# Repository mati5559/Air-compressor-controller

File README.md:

# Air-compressor-controller

Controller for my DIY air compressor

# Description

I made air compressor from two washing machine's motors, some tank, air pump and a few other elements. 
Those motors are universal brush motors, so i need some controller to stabilize their speed. 
This controller stabilises motors speed with PID algorithm, turns them on and off at specified pressure and have some other features:
- temperature protection
- oil change interval reminder (It measures working time and turn on LED when oil should be changed) 
- fan control 
- soft start (PID)
- overload protection

In software directory is Eclipse C++ project.
In hardware directory are board and schematic. It should be run with AutoDesk Eagle. 

# WARNING

DIY air compressors are very dangerous. 
There is high voltage in this circuit that can kill you.
High pressure tank also can be dangerous. It can explode.

I did it at my own risk for science and fun. Do not do this by yourself!

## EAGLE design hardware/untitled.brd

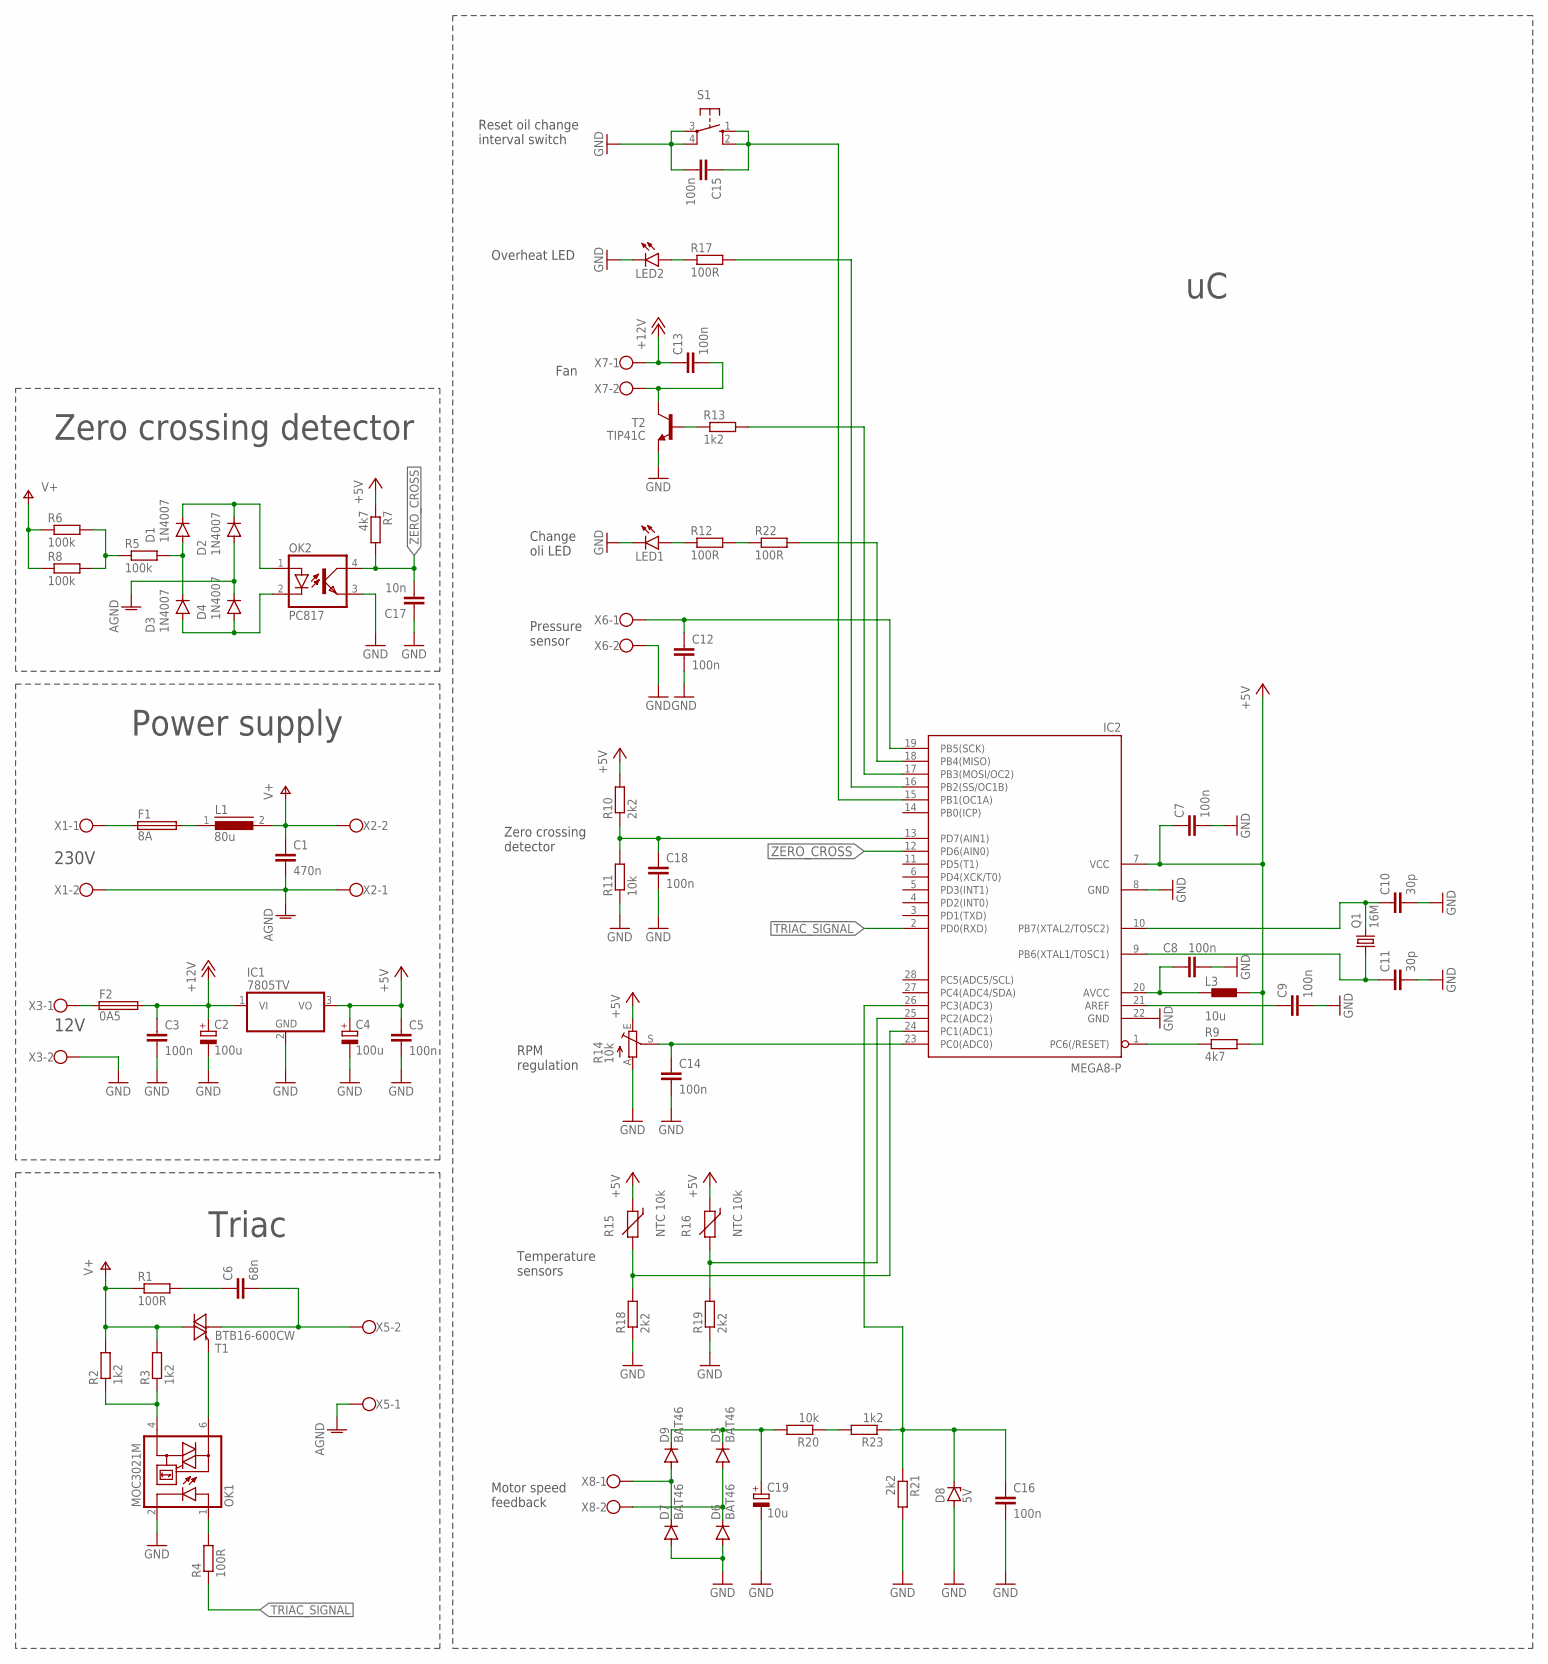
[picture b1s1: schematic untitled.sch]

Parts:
C1: 470n; C22.5B7
C2, C4: 100u; E3,5-8
C3, C5, C7, C8, C9, C12, C13, C14, C15, C16, C18: 100n; C5B3
C6: 68n; C150-084X183
C10, C11: 30p; C5B3
C17: 10n; C5B3
C19: 10u; E2,5-6
D1, D2, D3, D4: 1N4007; DO41-10
D5, D6, D7, D9: BAT46; DO34-7
D8: 5V; DO34Z7
F1: 8A; SHK20L
F2: 0A5; SHK20L
IC1: 7805TV; TO220V
IC2: MEGA8-P; DIL28-3
L1: 80u; SFT1030
L3: 10u; BL01RN1A
LED1, LED2: LED5MM
OK1: MOC3021M; DIL06
OK2: PC817; DIL04
Q1: 16M; HC49/S
R1, R4, R12, R17, R22: 100R; 0204/7
R2, R3, R13, R23: 1k2; 0204/7
R5, R6, R8: 100k; 0204/7
R7, R9: 4k7; 0204/7
R10, R18, R19, R21: 2k2; 0204/7
R11, R20: 10k; 0204/7
R14: 10k; RJ9W
R15, R16: NTC 10k; R-7,5
S1: 10-XX; B3F-10XX
T1: BTB16-600CW; TO220BV
T2: TIP41C; TO220V
X1, X2, X3, X5, X6, X7, X8: W237-102

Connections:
+5V: C4.+, C5.1, C7.1, IC1.3 (VO), IC2.7 (VCC), L3.2, R7.1, R9.2, R10.2, R14.E, R15.1, R16.1
+12V: C2.+, C3.1, C13.1, F2.2A, IC1.1 (VI), X7.1
AGND: C1.2, D2.A, D4.C, X1.2, X2.1, X5.1
GND: C2.-, C3.2, C4.-, C5.2, C7.2, C8.2, C9.2, C10.2, C11.2, C12.2, C14.2, C15.2, C16.2, C17.1, C18.2, C19.-, D6.A, D7.A, D8.A, IC1.2 (GND), IC2.8 (GND), IC2.22 (GND), LED1.K (C), LED2.K (C), OK1.2 (C), OK2.3 (EMIT), R11.1, R14.A, R18.1, R19.1, R21.2, S1.3, S1.4 (P1), T2.3 (E), X3.2, X6.2
unnamed: F1.1A, X1.1
unnamed: F1.2A, L1.1
unnamed: OK1.6 (A2), T1.G
unnamed: C6.2, T1.T1 (A1), X5.2
unnamed: C6.1, R1.2
unnamed: OK1.4 (A1), R2.1, R3.1
unnamed: F2.1A, X3.1
unnamed: OK1.1 (A), R4.2
unnamed: D1.C, D2.C, OK2.1 (A)
unnamed: D3.A, D4.A, OK2.2 (C)
unnamed: R5.1, R6.2, R8.2
unnamed: D7.C, D9.A, X8.1
unnamed: C18.1, IC2.13 (PD7(AIN1)), R10.1, R11.2
unnamed: C8.1, IC2.20 (AVCC), L3.1
unnamed: C9.1, IC2.21 (AREF)
unnamed: IC2.1 (PC6(/RESET)), R9.1
unnamed: C10.1, IC2.10 (PB7(XTAL2/TOSC2)), Q1.2
unnamed: C11.1, IC2.9 (PB6(XTAL1/TOSC1)), Q1.1
unnamed: C12.1, IC2.19 (PB5(SCK)), X6.1
unnamed: LED1.A, R12.1
unnamed: IC2.18 (PB4(MISO)), R22.2
unnamed: C13.2, T2.2 (C), X7.2
unnamed: R13.1, T2.1 (B)
unnamed: IC2.17 (PB3(MOSI/OC2)), R13.2
unnamed: C14.1, IC2.23 (PC0(ADC0)), R14.S
unnamed: IC2.24 (PC1(ADC1)), R15.2, R18.2
unnamed: IC2.25 (PC2(ADC2)), R16.2, R19.2
unnamed: LED2.A, R17.1
unnamed: IC2.16 (PB2(SS/OC1B)), R17.2
unnamed: C19.+, D5.C, D9.C, R20.2
unnamed: C15.1, IC2.15 (PB1(OC1A)), S1.1 (S), S1.2 (S1)
unnamed: D1.A, D3.C, R5.2
unnamed: D5.A, D6.C, X8.2
unnamed: C16.1, D8.C, IC2.26 (PC3(ADC3)), R21.1, R23.1
unnamed: R12.2, R22.1
unnamed: R20.1, R23.2
TRIAC_SIGNAL: IC2.2 (PD0(RXD)), R4.1
V+: C1.1, L1.2, R1.1, R2.2, R3.2, R6.1, R8.1, T1.T2 (A2), X2.2
ZERO_CROSS: C17.2, IC2.12 (PD6(AIN0)), OK2.4 (COL), R7.2

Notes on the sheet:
230V
12V
Power supply
Triac
Zero crossing detector
Pressure sensor
Change oli LED
Fan
RPM regulation
Temperature sensors
Overheat LED
Reset oil change interval switch
Motor speed feedback
Zero crossing detector

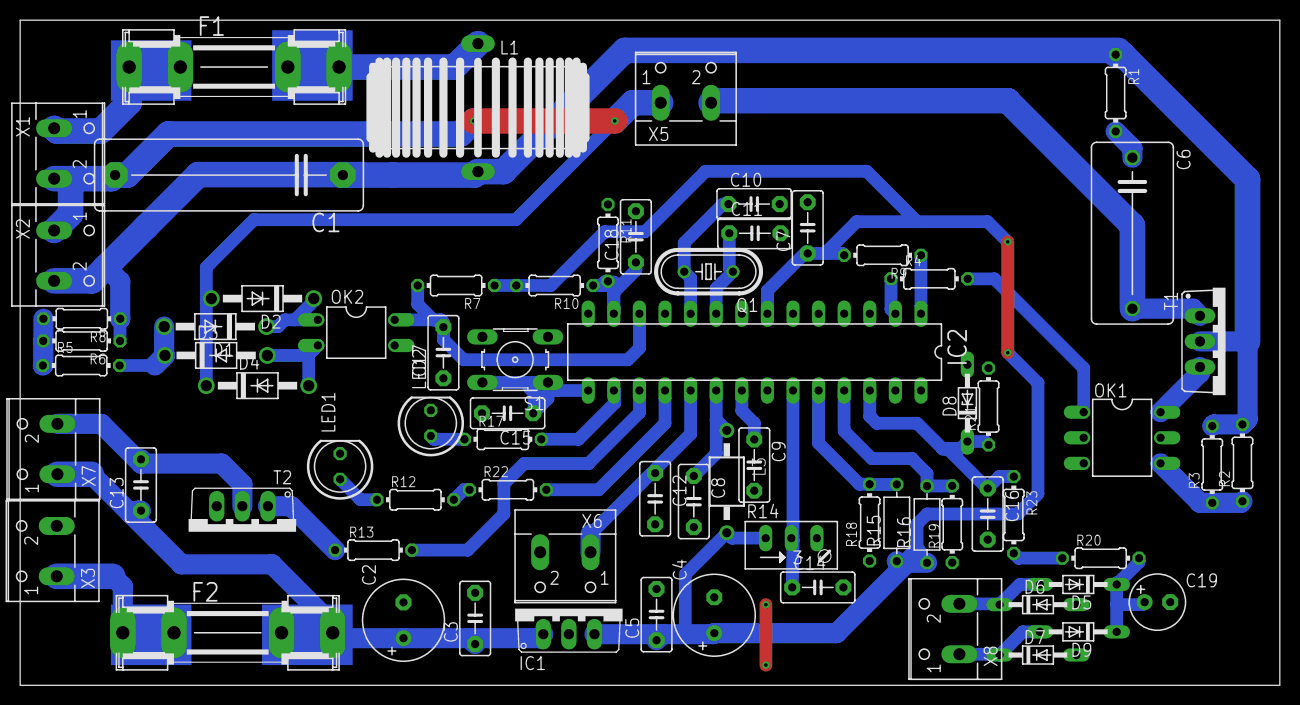
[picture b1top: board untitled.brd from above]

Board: 2 copper layers, 125.0 x 66.0 mm, 72 parts (0 on the bottom side), 43 nets.

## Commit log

2022-04-26 Implemented better ADC handling and some other small improvements
